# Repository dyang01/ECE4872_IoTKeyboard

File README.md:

# ECE4872_IoTKeyboard
Repository to store any files for the various hardware components of our project such as the PCB files and the 3D printing files

These include:
1. CAD files for the PCB
2. 3D Printing Files for the enclosure

Three of the following repositories are used for the IoTKeyboard. They provide the schematic and layout parts used in KiCad:
  - https://github.com/keebio/keebio-components
  - https://github.com/keebio/Keebio-Parts.pretty
  - https://github.com/ai03-2725/MX_Alps_Hybrid

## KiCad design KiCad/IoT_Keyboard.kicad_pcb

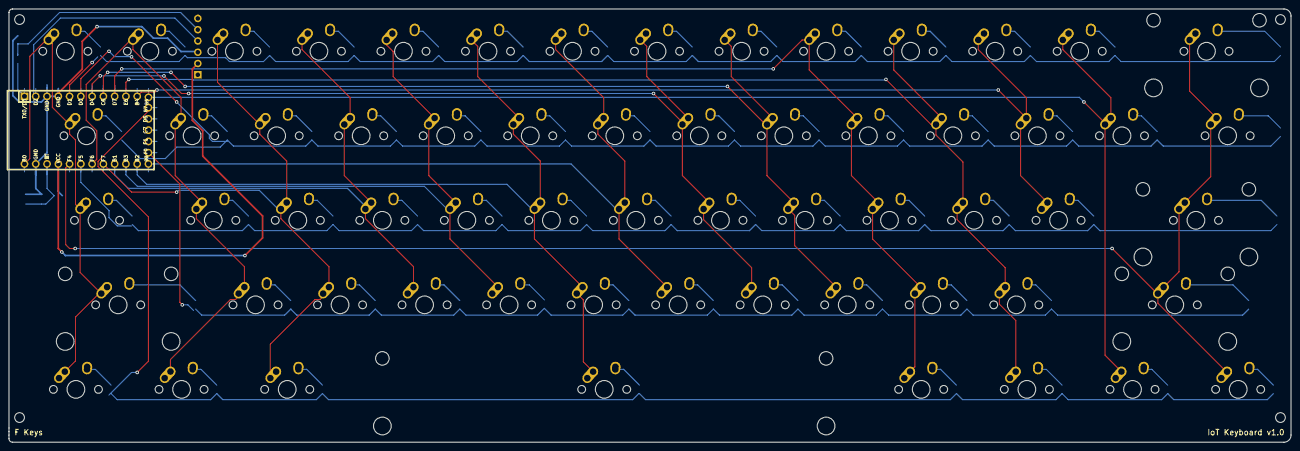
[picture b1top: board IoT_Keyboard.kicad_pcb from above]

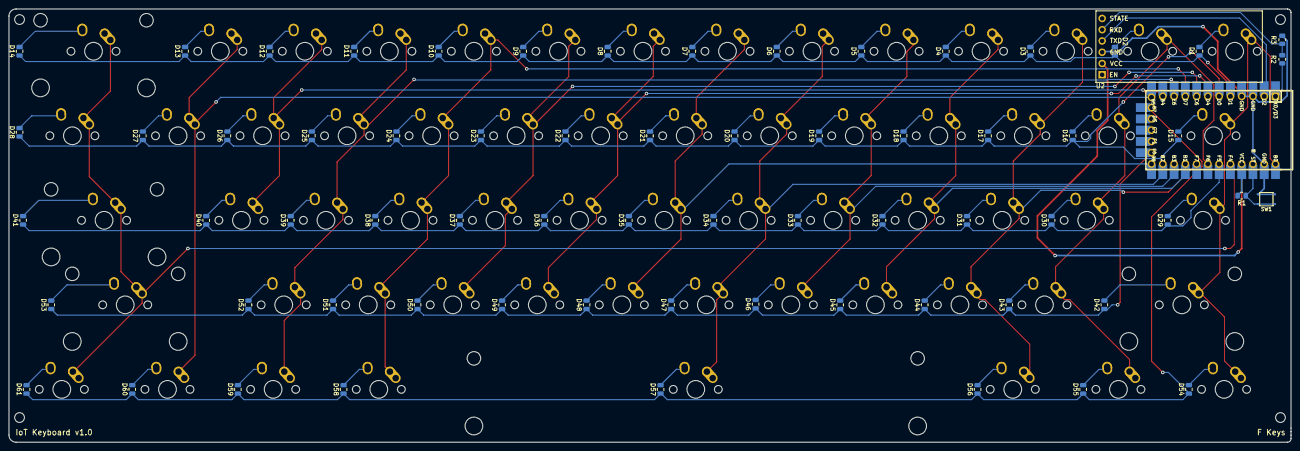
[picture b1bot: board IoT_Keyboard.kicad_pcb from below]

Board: 2 copper layers, 288.9 x 97.6 mm, 128 parts (67 on the bottom side), 86 nets.

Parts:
D1, D2, D3, D4, D5, D6, D7, D8, D9, D10, D11, D12, D13, D14, D15, D16, D17, D18, D19, D20, D21, D22, D23, D24, D25, D26, D27, D28, D29, D30, D31, D32, D33, D34, D35, D36, D37, D38, D39, D40, D41, D42, D43, D44, D45, D46, D47, D48, D49, D50, D51, D52, D53, D54, D55, D56, D57, D58, D59, D60, D61: SOD-123; C_0805_2012Metric
MX1, MX2, MX3, MX4, MX5, MX6, MX7, MX8, MX9, MX10, MX11, MX12, MX13, MX16, MX17, MX18, MX19, MX20, MX21, MX22, MX23, MX24, MX25, MX26, MX27, MX30, MX31, MX32, MX33, MX34, MX35, MX36, MX37, MX38, MX39, MX40, MX43, MX44, MX45, MX46, MX47, MX48, MX49, MX50, MX51, MX52: MX-NoLED; MX-1U-NoLED
MX14: MX-NoLED; MX-2U-NoLED
MX15, MX28: MX-NoLED; MX-1.5U-NoLED
MX29: MX-NoLED; MX-1.75U-NoLED
MX41, MX42: MX-NoLED; MX-2.25U-NoLED
MX53: MX-NoLED; MX-2.75U-NoLED
MX54, MX55, MX56, MX58, MX59, MX60, MX61: MX-NoLED; MX-1.25U-NoLED
MX57: MX-NoLED; MX-6.25U-NoLED
R1: 10k; R_0805_2012Metric
R2: 1k; R_0805_2012Metric
R3: 2k; R_0805_2012Metric
SW1: SW_Push; SW_SPST_3x3
U1: Elite-C; Elite-C-castellated-29pin-holes
U2: HC-05

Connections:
COL0: MX1.1, MX15.1, MX29.1, MX42.1, MX54.1, U1.24
COL1: MX2.1, MX16.1, MX30.1, MX43.1, MX55.1, U1.18
COL2: MX3.1, MX17.1, MX31.1, MX44.1, MX56.1, U1.17
COL3: MX4.1, MX18.1, MX32.1, MX45.1, U1.16
COL4: MX5.1, MX19.1, MX33.1, MX46.1, U1.15
COL5: MX6.1, MX20.1, MX34.1, MX47.1, MX57.1, U1.14
COL6: MX7.1, MX21.1, MX35.1, MX48.1, U1.13
COL7: MX8.1, MX22.1, MX36.1, MX49.1, U1.7
COL8: MX9.1, MX23.1, MX37.1, MX50.1, U1.8
COL9: MX10.1, MX24.1, MX38.1, MX51.1, MX58.1, U1.9
COL10: MX11.1, MX25.1, MX39.1, MX52.1, MX59.1, U1.10
COL11: MX12.1, MX26.1, MX40.1, U1.11
COL12: MX13.1, MX27.1, MX60.1, U1.12
COL13: MX14.1, MX28.1, MX41.1, MX53.1, MX61.1, U1.20
GND: R3.1, SW1.2, U1.3, U1.4, U1.23, U2.3
unnamed: D1.2, MX1.2
unnamed: D2.2, MX2.2
unnamed: D3.2, MX3.2
unnamed: D4.2, MX4.2
unnamed: D5.2, MX5.2
unnamed: D6.2, MX6.2
unnamed: D7.2, MX7.2
unnamed: D8.2, MX8.2
unnamed: D9.2, MX9.2
unnamed: D10.2, MX10.2
unnamed: D11.2, MX11.2
unnamed: D12.2, MX12.2
unnamed: D13.2, MX13.2
unnamed: D14.2, MX14.2
unnamed: D15.2, MX15.2
unnamed: D16.2, MX16.2
unnamed: D17.2, MX17.2
unnamed: D18.2, MX18.2
unnamed: D19.2, MX19.2
unnamed: D20.2, MX20.2
unnamed: D21.2, MX21.2
unnamed: D22.2, MX22.2
unnamed: D23.2, MX23.2
unnamed: D24.2, MX24.2
unnamed: D25.2, MX25.2
unnamed: D26.2, MX26.2
unnamed: D27.2, MX27.2
unnamed: D28.2, MX28.2
unnamed: D29.2, MX29.2
unnamed: D30.2, MX30.2
unnamed: D31.2, MX31.2
unnamed: D32.2, MX32.2
unnamed: D33.2, MX33.2
unnamed: D34.2, MX34.2
unnamed: D35.2, MX35.2
unnamed: D36.2, MX36.2
unnamed: D37.2, MX37.2
unnamed: D38.2, MX38.2
unnamed: D39.2, MX39.2
unnamed: D40.2, MX40.2
unnamed: D41.2, MX41.2
unnamed: D42.2, MX42.2
unnamed: D43.2, MX43.2
unnamed: D44.2, MX44.2
unnamed: D45.2, MX45.2
unnamed: D46.2, MX46.2
unnamed: D47.2, MX47.2
unnamed: D48.2, MX48.2
unnamed: D49.2, MX49.2
unnamed: D50.2, MX50.2
unnamed: D51.2, MX51.2
unnamed: D52.2, MX52.2
unnamed: D53.2, MX53.2
unnamed: D54.2, MX54.2
unnamed: D55.2, MX55.2
unnamed: D56.2, MX56.2
unnamed: D57.2, MX57.2
unnamed: D58.2, MX58.2
unnamed: D59.2, MX59.2
unnamed: D60.2, MX60.2
unnamed: D61.2, MX61.2
unnamed: R1.1, SW1.1, U1.22
unnamed: R1.2, U1.21, U2.2
unnamed: R2.1, R3.2, U2.5
unnamed: R2.2, U1.1
unnamed: U1.2, U2.4
ROW0: D1.1, D2.1, D3.1, D4.1, D5.1, D6.1, D7.1, D8.1, D9.1, D10.1, D11.1, D12.1, D13.1, D14.1, U1.5
ROW1: D15.1, D16.1, D17.1, D18.1, D19.1, D20.1, D21.1, D22.1, D23.1, D24.1, D25.1, D26.1, D27.1, D28.1, U1.6
ROW2: D29.1, D30.1, D31.1, D32.1, D33.1, D34.1, D35.1, D36.1, D37.1, D38.1, D39.1, D40.1, D41.1, U1.19
ROW3: D42.1, D43.1, D44.1, D45.1, D46.1, D47.1, D48.1, D49.1, D50.1, D51.1, D52.1, D53.1, U1.29
ROW4: D54.1, D55.1, D56.1, D57.1, D58.1, D59.1, D60.1, D61.1, U1.25

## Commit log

2021-02-06 Added basic Kicad project and Keebio Library
2021-02-06 Create hello.txt
    I created a text file to test if II could push from github desktop
2021-02-07 Create IoT_Keyboard.sch-bak
2021-02-07 Create sym-lib-table
2021-02-07 Update fp-lib-table
2021-02-07 Update fp-info-cache
2021-02-13 Update README.md
    fixed newline?
2021-02-13 Update README.md
    hi armin
2021-02-13 Changed/Added Libraries (ai03). Added key matrix/images to separate sheet
2021-02-21 Update README.md
    Added the repositories used in the keyboard design
2021-02-21 Changed gitignore not include lib
    The library files for KiCad were not added properly. Changed the .gitignore
2021-02-24 Parts of the pcb laid out
2021-02-25 Update sym-lib-table
2021-02-27 Wired Rows/Cols of Switches. Created Physical PCB.
2021-02-27 Added HC-05 Schematic
2021-02-27 Routed rows and columsn to microcontroller with Daniel
    :)
2021-02-27 Added HC-05 to PCB and routed. Added mounting holes. Generated gerbers
2021-03-02 Added Keyboard Dimensions
2021-03-05 Cleaned Up the Repo and Changed Readme
